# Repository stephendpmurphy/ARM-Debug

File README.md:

# ARCHIVED - ARM Debug Board

## This project has been archived, and is being redesigned in KiCAD. The project can be found here: [swd-debug](https://github.com/stephendpmurphy/swd-debug)

This debug board allows two unused traces of a 10pin JTAG/SWD connector (Pins 7 & 9) to be broken out and used for a UART RX & TX line from the target MCU. These UART lines can be used by the Target to send debug print statements through the programming connector, to the USB bridge, and then displayed on a PC terminal. This is useful since board space is no longer needed on the target for any sort of extra headers or test pads for debug data.

All components are included via a managed library on my account. Create an issue on this repo to request access.

Note: This can only be used with Targets that use SWD as the programming interface. A different board will need to be made in the case the pinout changes of the Samtech Cortex header (TPI, SPI, etc.)

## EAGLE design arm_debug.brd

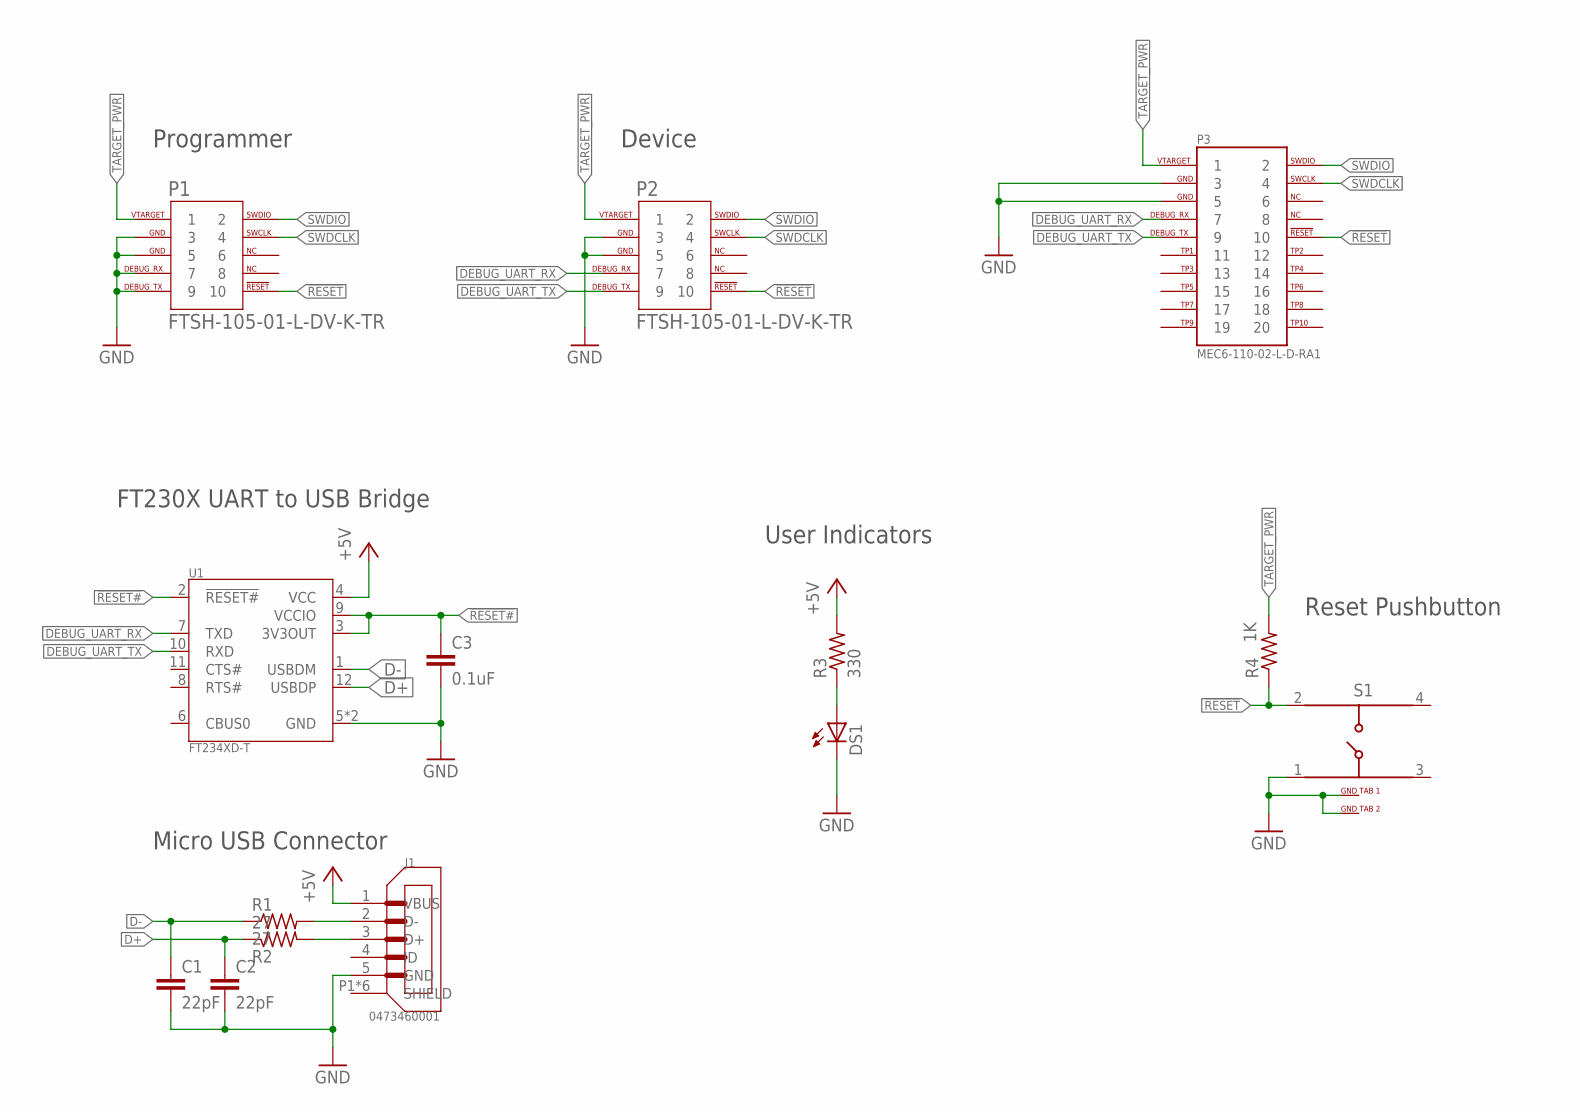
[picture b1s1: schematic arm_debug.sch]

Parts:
C1, C2: 22pF; M0603
C3: 0.1uF; M0603
DS1: LED0603; 0603
J1: 0473460001; 047346-0001
P1, P2: FTSH-105-01-L-DV-K-TR; SAMTEC_FTSH-105-01-L-DV-K
P3: MEC6-110-02-L-D-RA1; MEC6-110-02-X-D-RAX-F
R1, R2: 27; M0603
R3: 330; M0603
R4: 1K; M0603
S1: 431181015816
U1: FT234XD-T; DFN-12

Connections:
!RESET: P1.10, P2.10, P3.10, R4.1, S1.2
!RESET#: C3.1, U1.2 (!RESET#), U1.3 (3V3OUT), U1.9 (VCCIO)
+5V: J1.1 (VBUS), R3.2, U1.4 (VCC)
D+: C2.1, R2.1, U1.12 (USBDP)
D-: C1.1, R1.1, U1.1 (USBDM)
DEBUG_UART_RX: P2.7, P3.7, U1.7 (TXD)
DEBUG_UART_TX: P2.9, P3.9, U1.10 (RXD)
GND: C1.2, C2.2, C3.2, DS1.C, J1.5 (GND), P1.3, P1.5, P1.7, P1.9, P2.3, P2.5, P3.3, P3.5, S1.1, S1.GND1 (6), S1.GND2 (5), U1.5 (GND), U1.13 (GND)
unnamed: J1.2 (D-), R1.2
unnamed: DS1.A, R3.1
unnamed: J1.3 (D+), R2.2
SWDCLK: P1.4, P2.4, P3.4
SWDIO: P1.2, P2.2, P3.2
TARGET_PWR: P1.1, P2.1, P3.1, R4.2

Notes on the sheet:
Programmer
Device
Micro USB Connector
FT230X UART to USB Bridge
User Indicators
Reset Pushbutton

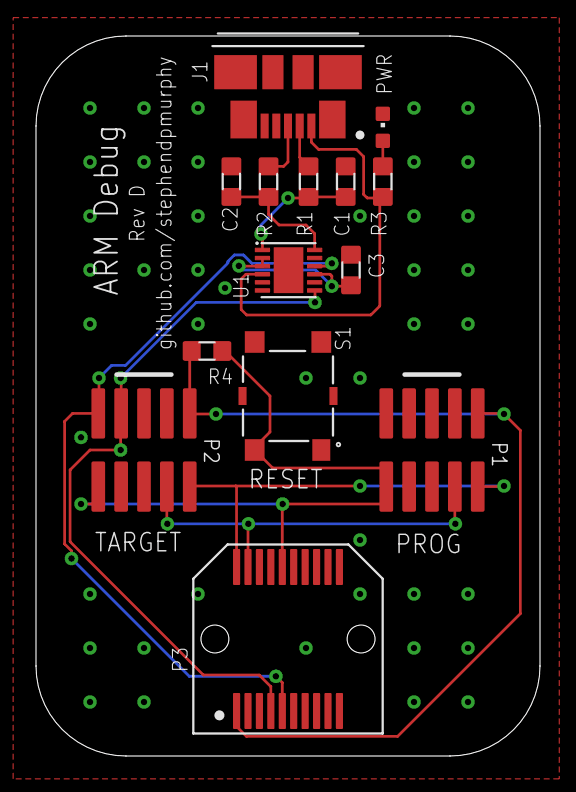
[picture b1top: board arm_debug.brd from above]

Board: 2 copper layers, 28.0 x 40.0 mm, 14 parts (0 on the bottom side), 14 nets.

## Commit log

2018-05-19 Adding Rev A
2018-05-19 Adding pictures of board and schematic
2018-05-19 Adding schematic PDF
2018-05-20 Fixing airwire between 5V LED and resistor
2018-05-21 Set theme jekyll-theme-tactile
2018-05-21 Set theme jekyll-theme-cayman
2018-05-21 Set theme jekyll-theme-slate
2018-05-25 Removing files from Jekyl site
2018-05-28 Saving place.. currently working on Rev B
2018-08-19 Committing RevB
2019-01-05 Commiting RevC
2019-04-21 Adding MEC connector for edge card connectors
2019-04-21 Fixed DRC error with VIA too close to trace
2019-10-29 Fixing issue with reversed USB Data plus and minus pins
2019-11-12 Seperating passive components into individual managed libraries

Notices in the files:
README.md:
CC by SA
parts and their libraries:
programming_headers: ©2009 ROFA.cz
